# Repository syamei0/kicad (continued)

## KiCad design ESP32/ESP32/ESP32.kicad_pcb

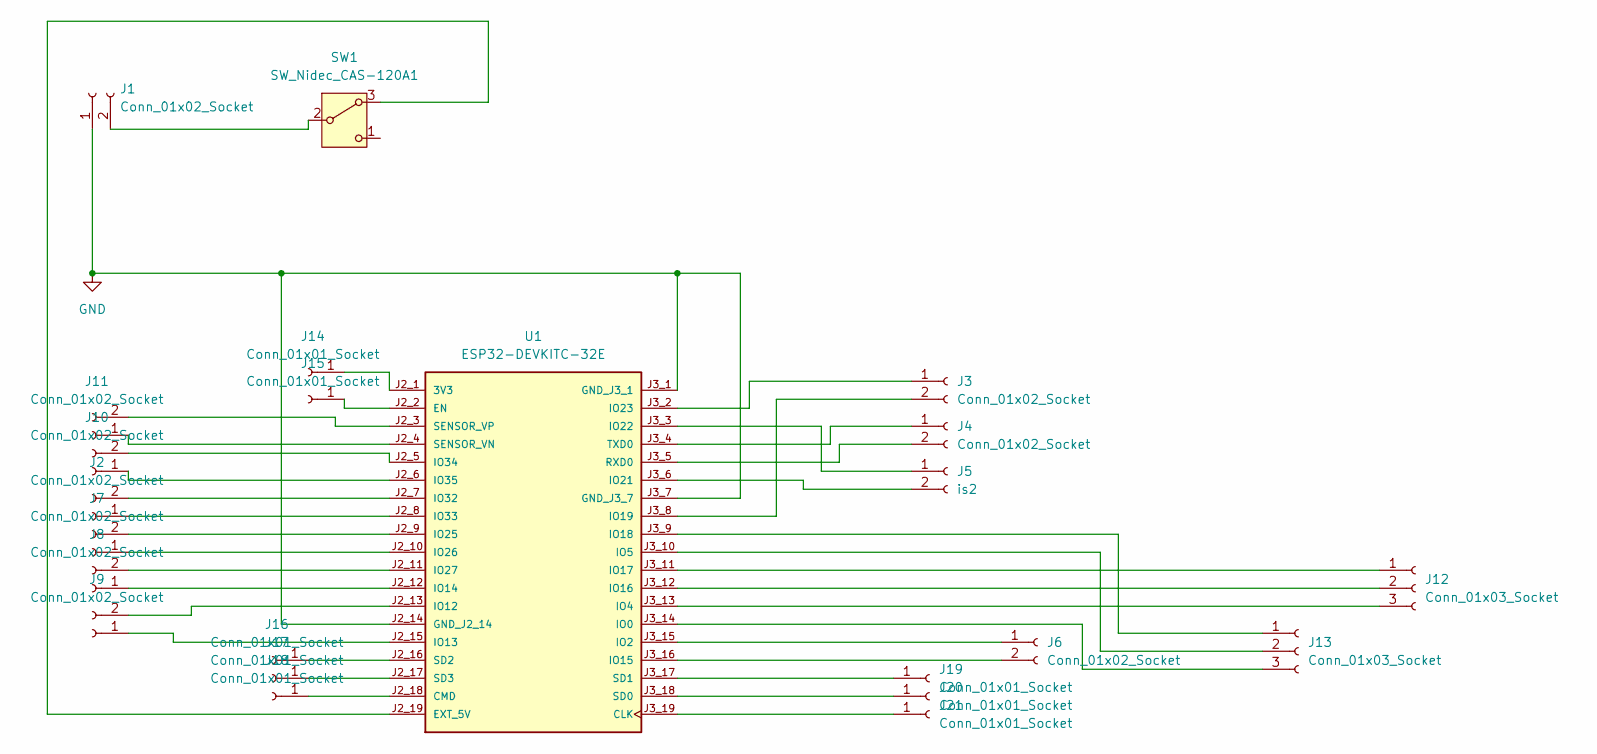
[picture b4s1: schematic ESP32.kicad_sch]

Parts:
J1: Conn_01x02_Socket; JST_XH_B2B-XH-AM_1x02_P2.50mm_Vertical
J2, J3, J4, J6, J7, J8, J9, J10, J11: Conn_01x02_Socket; JST_EH_B2B-EH-A_1x02_P2.50mm_Vertical
J5: is2; JST_EH_B2B-EH-A_1x02_P2.50mm_Vertical
J12, J13: Conn_01x03_Socket; JST_EH_B3B-EH-A_1x03_P2.50mm_Vertical
J14, J15, J16, J17, J18, J19, J20, J21: Conn_01x01_Socket; JST_XH_B1B-XH-AM_1x01_P2.50mm_Vertical
SW1: SW_Nidec_CAS-120A1; TerminalBlock_Xinya_XY308-2.54-3P_1x03_P2.54mm_Horizontal
U1: ESP32-DEVKITC-32E; MODULE_ESP32-DEVKITC-32E; PARTREV 1.4

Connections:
GND: J1.1, U1.J2_14 (GND_J2_14), U1.J3_1 (GND_J3_1), U1.J3_7 (GND_J3_7)
unnamed: J1.2, SW1.2 (B)
unnamed: J2.1, U1.J2_8 (IO33)
unnamed: J2.2, U1.J2_7 (IO32)
unnamed: J3.1, U1.J3_2 (IO23)
unnamed: J3.2, U1.J3_8 (IO19)
unnamed: J4.1, U1.J3_4 (TXD0)
unnamed: J4.2, U1.J3_5 (RXD0)
unnamed: J5.1, U1.J3_3 (IO22)
unnamed: J5.2, U1.J3_6 (IO21)
unnamed: J6.1, U1.J3_15 (IO2)
unnamed: J6.2, U1.J3_16 (IO15)
unnamed: J7.1, U1.J2_10 (IO26)
unnamed: J7.2, U1.J2_9 (IO25)
unnamed: J8.1, U1.J2_12 (IO14)
unnamed: J8.2, U1.J2_11 (IO27)
unnamed: J9.1, U1.J2_15 (IO13)
unnamed: J9.2, U1.J2_13 (IO12)
unnamed: J10.1, U1.J2_6 (IO35)
unnamed: J10.2, U1.J2_5 (IO34)
unnamed: J11.1, U1.J2_4 (SENSOR_VN)
unnamed: J11.2, U1.J2_3 (SENSOR_VP)
unnamed: J12.1, U1.J3_11 (IO17)
unnamed: J12.2, U1.J3_12 (IO16)
unnamed: J12.3, U1.J3_13 (IO4)
unnamed: J13.1, U1.J3_9 (IO18)
unnamed: J13.2, U1.J3_10 (IO5)
unnamed: J13.3, U1.J3_14 (IO0)
unnamed: J14.1, U1.J2_1 (3V3)
unnamed: J15.1, U1.J2_2 (EN)
unnamed: J16.1, U1.J2_16 (SD2)
unnamed: J17.1, U1.J2_17 (SD3)
unnamed: J18.1, U1.J2_18 (CMD)
unnamed: J19.1, U1.J3_17 (SD1)
unnamed: J20.1, U1.J3_18 (SD0)
unnamed: J21.1, U1.J3_19 (CLK)
unnamed: SW1.3 (A), U1.J2_19 (EXT_5V)

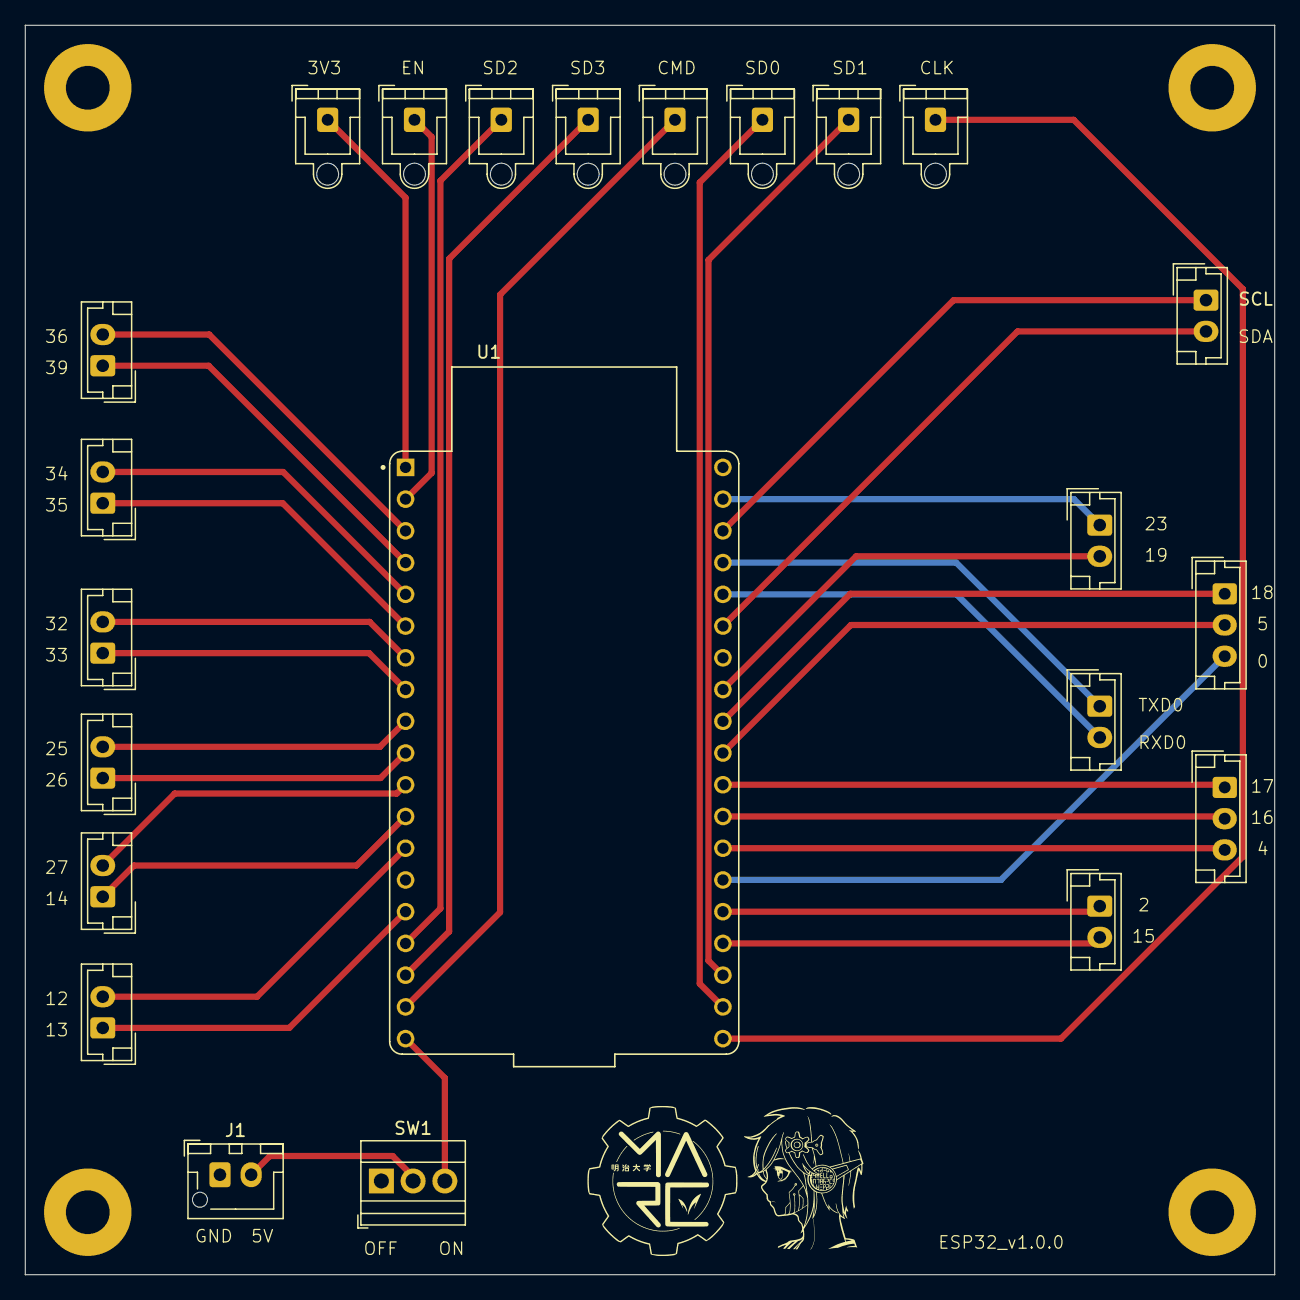
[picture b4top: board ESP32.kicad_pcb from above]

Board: 2 copper layers, 100.0 x 100.0 mm, 23 parts (0 on the bottom side), 37 nets.

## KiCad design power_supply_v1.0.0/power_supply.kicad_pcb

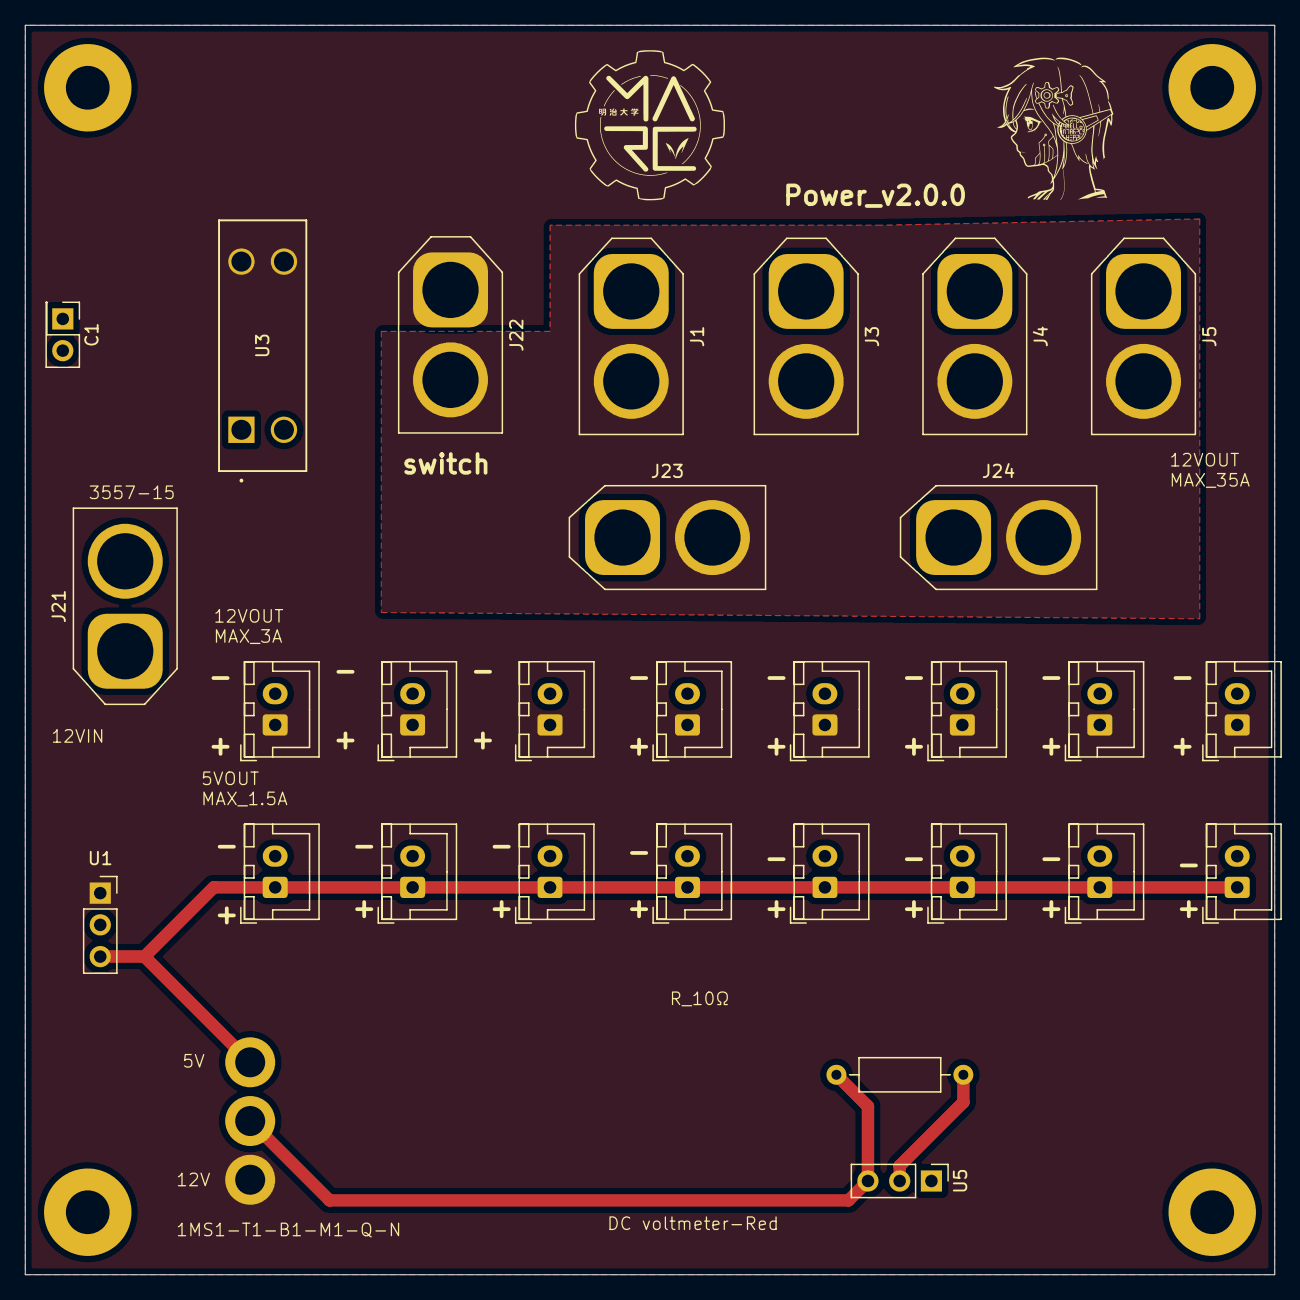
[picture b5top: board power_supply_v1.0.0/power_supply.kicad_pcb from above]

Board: 2 copper layers, 100.0 x 100.0 mm, 30 parts (0 on the bottom side), 7 nets.

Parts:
C1: C; PinHeader_2x01_P2.54mm_Vertical
J1, J3, J4, J5, J23, J24: Conn_01x02_Socket; AMASS_XT60-F_1x02_P7.20mm_Vertical
J2, J6, J7, J8, J9, J10, J11, J12, J13, J14, J15, J16, J17, J18, J19, J20: Conn_01x02_Socket; JST_XH_B2B-XH-A_1x02_P2.50mm_Vertical
J21, J22: Conn_01x02_Pin; AMASS_XT60-F_1x02_P7.20mm_Vertical
R1: 10; R_Axial_DIN0207_L6.3mm_D2.5mm_P10.16mm_Horizontal
U1: PinSocket_1x03_P2.54mm_Vertical
U3: 3557-15_KEY
U4: 1MS1-T1-B1-M1-Q-N-S
U5: PinHeader_1x03_P2.54mm_Vertical

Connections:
+12V_1: C1.2, J21.2 (VCC), U3.1, U3.2
+12V_2: J6.1, J7.1, J8.1, J9.1, J10.1, J11.1, J12.1, J13.1, J22.1 (GND), U1.1 (VIN), U3.3, U3.4, U4.3
+12V_3: J1.2, J3.2, J4.2, J5.2, J22.2 (VCC), J23.2, J24.2
GND: C1.1, J1.1, J2.2, J3.1, J4.1, J5.1, J6.2, J7.2, J8.2, J9.2, J10.2, J11.2, J12.2, J13.2, J14.2, J15.2, J16.2, J17.2, J18.2, J19.2, J20.2, J21.1 (GND), J23.1, J24.1, U1.2 (GND), U5.1 (GND)
unnamed: J2.1, J14.1, J15.1, J16.1, J17.1, J18.1, J19.1, J20.1, U1.3 (VOUT), U4.1
unnamed: R1.1, U5.2
unnamed: R1.2, U4.2, U5.3 (OUT)

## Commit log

2024-10-03 test
2024-10-05 名前変更
2024-10-07 v1.0.1
2024-10-07 v1.0.0
2024-10-08 設定ファイル
    フットプリントとシンボルデータ
2024-10-08 2024/10/8
2024-10-10 v1.1.0
    ・3端子レギュレータを追加
    ・ポリスイッチを追加
    ・配線を改良
2024-10-15 2024/10/15
2024-11-05 2024/11/05
2024-11-05 2024/11/05/23:24
2024-11-08 2024/11/08
2024-11-18 2024/11/18
2024-11-19 2024/11/19
2024-12-01 USB-cポートとシリアル変換を乗せた
2024-12-04 逆起電力用ダイオード追加,小型リレーのフットプリント修正,大型リレーのスイッチを反転
2024-12-14 2.1.0
2024-12-17 RJ45フットプリント修正,CH340E→CH340K
